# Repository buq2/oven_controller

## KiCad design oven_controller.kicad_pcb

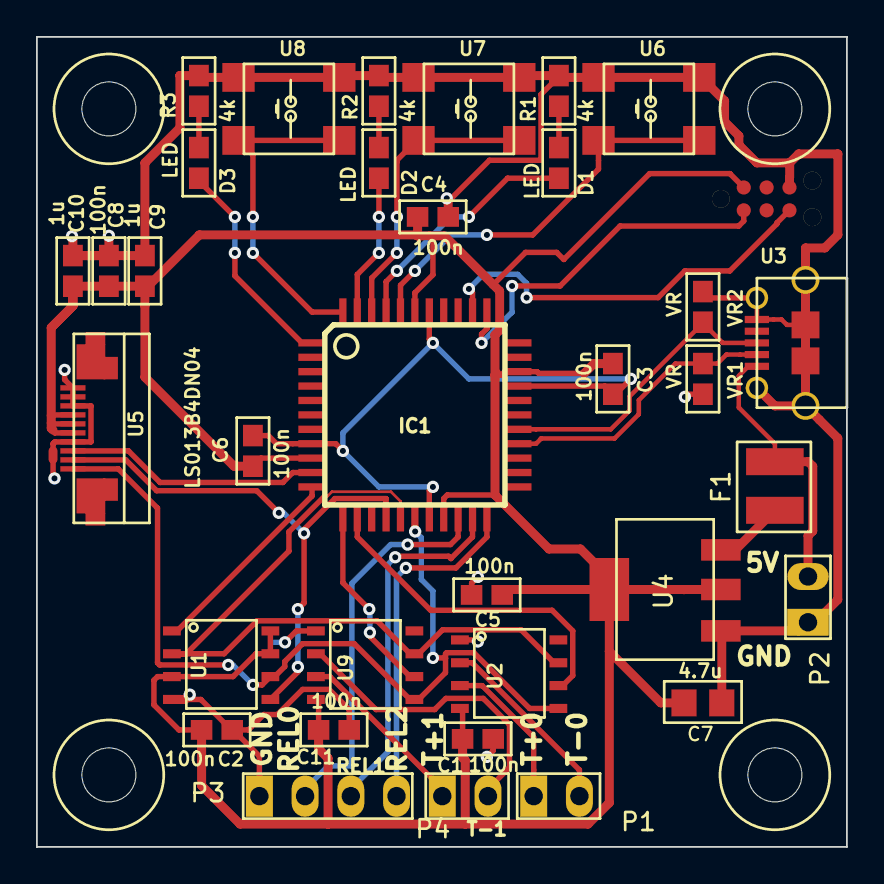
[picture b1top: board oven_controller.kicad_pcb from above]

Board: 2 copper layers, 45.0 x 45.0 mm, 39 parts (0 on the bottom side), 31 nets.

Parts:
C1, C2, C3, C4, C5, C6, C8, C11: 100n; SM0603
C7: 4.7u; SM0805
C9, C10: 1u; SM0603
CON1: BUQ2-USB-MICRO-B; USB-MICRO-B-FCI-10118194
D1, D2, D3: LED; SM0603
F1: FUSE; RESETTABLE_FUSE_BOURNS
IC1: BUQ2-ATXMEGA128A4U-A; BUQ2-TQFP44
MOUNTING_HOLE: VAL**; MOUNTING_HOLE
MOUNTING_HOLE#2, MOUNTING_HOLE#3, MOUNTING_HOLE#4: VAL**; MOUNTING_HOLE
P1: CONN_THERMO0; PIN_HEADER_2
P2: CONN_POWER; PIN_HEADER_2
P3: CONN_4; PIN_HEADER_4
P4: CONN_THERMO1; PIN_HEADER_2
R1, R2, R3: 4k; SM0603
U1: FLASH_MEMORY; 8-SOIC
U2, U9: MAX6675ISA+; 8-SOIC
U3: TAG-CONNECT-ATMEL-PDI-CONNECTOR; TAG-CONNECT6
U4: LD1117-SOT-223; SOT-223
U5: LS013B4DN04; FPC-CONN-10-FCI-TOP-CONTACTS
U6, U7, U8: SW_PUSH_4_PIN; PUSHBUTTON_4x4_5x5_ROTATED_4_PIN
VR1, VR2: VR; SM0603

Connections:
/BTN0: IC1.40, U6.1, U6.2
/BTN1: IC1.42, U7.1, U7.2
/BTN2: IC1.44, U8.1, U8.2
/CS_DISPLAY: IC1.10, U5.3
/CSn_FLASH: IC1.11, U1.1
/D+: CON1.3, IC1.27, VR2.1
/D-: CON1.2, IC1.26, VR1.2
/LD0: D1.1, IC1.41
/LD1: D2.1, IC1.43
/LD2: D3.1, IC1.1
/MISO: IC1.16, U1.2, U2.7, U9.7
/MOSI: IC1.15, U1.5, U5.2
/PDI_CLK: IC1.35, U3.5
/PDI_DATA: IC1.34, U3.1
/RELAY0: IC1.20, P3.2
/RELAY1: IC1.21, P3.3
/RELAY2: IC1.22, P3.4
/SCK: IC1.17, U1.6, U2.5, U5.1, U9.5
/T+0: P1.1, U2.3
/T+1: P4.1, U9.3
/T-0: P1.2, U2.2
/T-1: P4.2, U9.2
/VBUS: CON1.1, F1.1, P2.2
/VDD: C1.1, C2.2, C3.2, C4.2, C5.2, C6.2, C7.1, C8.1, C9.1, C10.1, C11.1, IC1.9, IC1.19, IC1.31, IC1.39, U1.3, U1.7, U1.8, U2.4, U3.2, U4.2, U5.5, U5.6, U5.7, U9.4
/nCS_THERMO0: IC1.13, U2.6
/nCS_THERMO1: IC1.12, U9.6
GND: C1.2, C2.1, C3.1, C4.1, C5.1, C6.1, C7.2, C8.2, C9.2, C10.2, C11.2, CON1.5, CON1.6, IC1.8, IC1.18, IC1.30, IC1.38, P2.1, P3.1, R1.1, R2.1, R3.1, U1.4, U2.1, U3.6, U4.1, U5.4, U5.8, U5.9, U5.10, U6.3, U6.4, U7.3, U7.4, U8.3, U8.4, U9.1, VR1.1, VR2.2
unnamed: D1.2, R1.2
unnamed: D2.2, R2.2
unnamed: D3.2, R3.2
unnamed: F1.2, U4.3

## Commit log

2015-01-20 Init
2015-01-20 Layout done, but not checked
2015-02-05 Ordered v1
2015-02-18 Move board files to different folder
2015-02-18 Started implementing mcu code
2015-02-22 Working. PID needs better parameters
